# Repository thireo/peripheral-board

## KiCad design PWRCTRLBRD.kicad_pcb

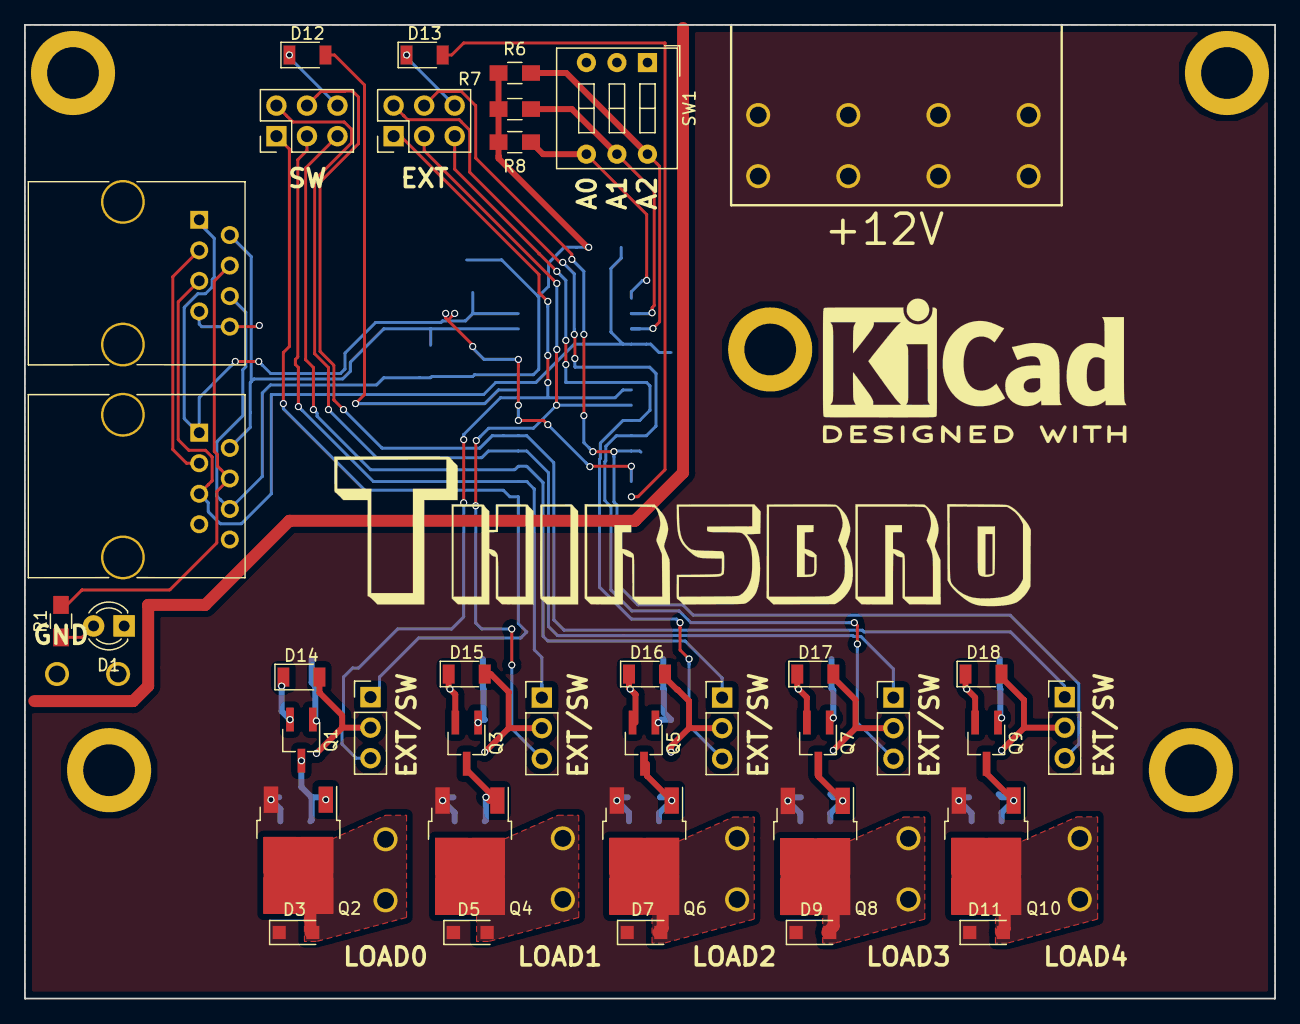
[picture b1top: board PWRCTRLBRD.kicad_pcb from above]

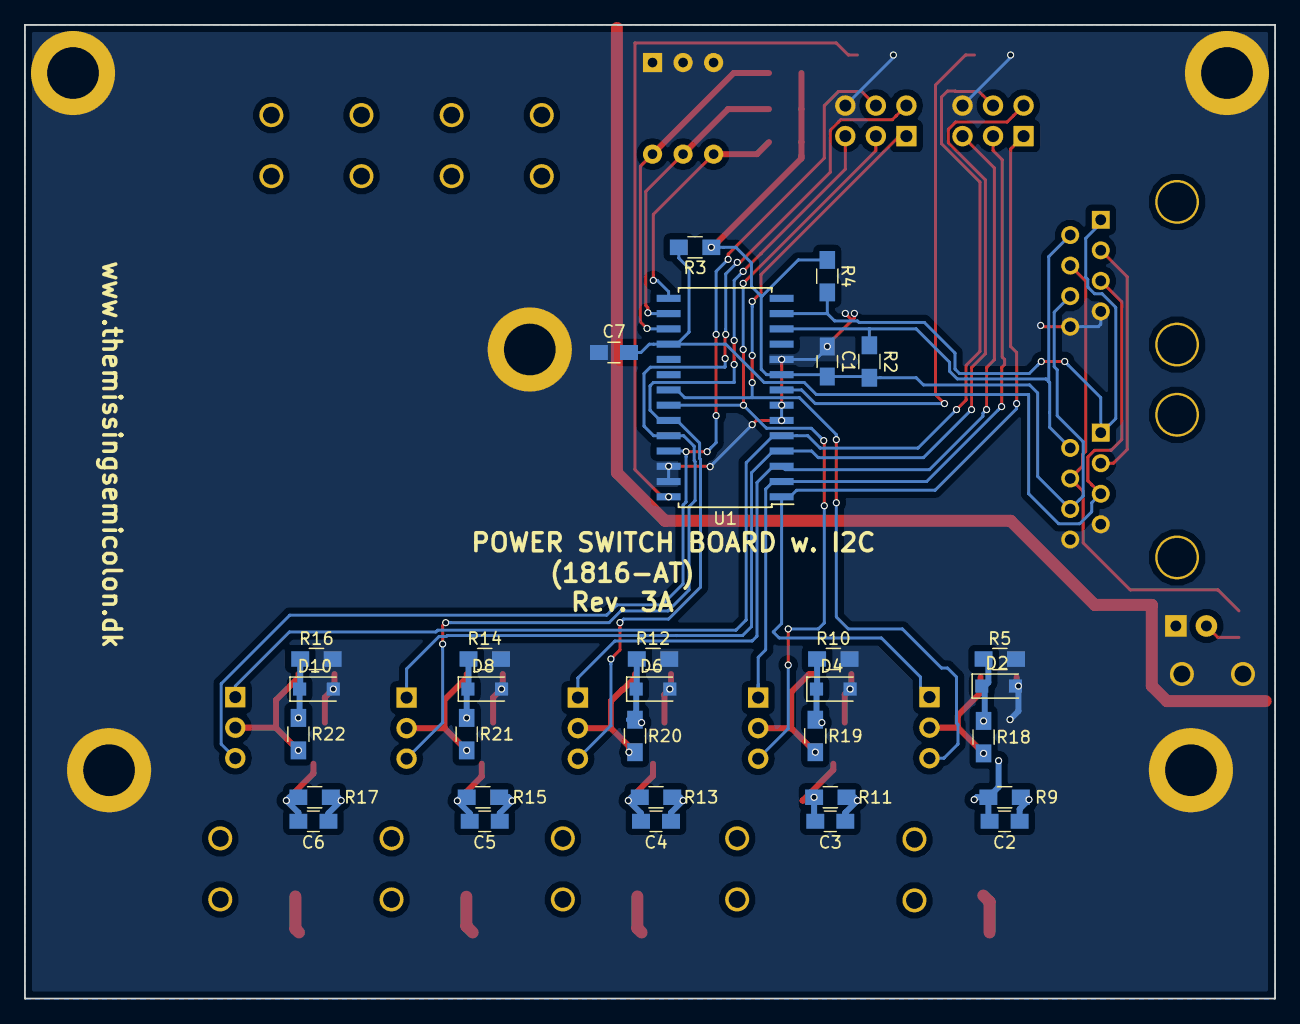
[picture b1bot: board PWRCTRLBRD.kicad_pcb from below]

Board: 2 copper layers, 104.0 x 81.0 mm, 79 parts (31 on the bottom side), 44 nets.

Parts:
C1, C2, C3, C4, C5, C6, C7: 10uF; C_0805_HandSoldering
D1: LED; LED_D3.0mm
D2, D4, D6, D8, D10: GS-TVS; D_SOD-123F
D3, D5, D7, D9, D11: DS-TVS; D_SOD-123F
D12: SW; D_1206
D13: EXT; D_1206
D14: SW0; D_1206
D15: SW1; D_1206
D16: SW2; D_1206
D17: SW3; D_1206
D18: SW4; D_1206
GND: MountingHole_4.3mm_M4_ISO14580_Pad
J1, J5, J6, J7, J8: Screw_Terminal_01x01; FASTON63951-1
J9: LOAD0; FASTON63951-1
J10: CTRL_IN1; RJ45_8
J11: CTRL0; RJ45_8
J12: LOAD1; FASTON63951-1
J13: LOAD2; FASTON63951-1
J14: LOAD3; FASTON63951-1
J15: LOAD4; FASTON63951-1
J16: EXT_IN; Pin_Header_Straight_2x03_Pitch2.54mm
J17: EXT_OUT; Pin_Header_Straight_2x03_Pitch2.54mm
JP2, JP3, JP4, JP5, JP6: EXT/SW; Pin_Header_Straight_1x03_Pitch2.54mm
Q1, Q3, Q5, Q7, Q9: NTR5103NT1G; TSOT-23_HandSoldering
Q2, Q4, Q6, Q8, Q10: TP0610T; TO-252-2
R1: R_LED; R_0805_HandSoldering
R2, R3, R4, R5, R6, R7, R8, R9, R10, R11, R12, R13, R14, R15, R16, R17: 10kohm; R_0805_HandSoldering
R18, R19, R20, R21, R22: 200ohm; R_0805_HandSoldering
SW1: SW_DIP_x03; SW_DIP_x3_W7.62mm_Slide
U1: MCP23017; SOIC-28W_7.5x17.9mm_Pitch1.27mm

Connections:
+12V: C2.1, C3.1, C4.1, C5.1, C6.1, D3.1, D5.1, D7.1, D9.1, D11.1, J5.1, J6.1, J7.1, J8.1, Q2.3, Q4.3, Q6.3, Q8.3, Q10.3, R9.1, R11.1, R13.1, R15.1, R17.1
/CS: J10.3, J11.3
/EXT0: J17.1, JP2.3, U1.21
/EXT1: J17.3, JP3.3, U1.22
/EXT2: J17.5, JP4.3, U1.23
/EXT3: J17.2, JP5.3, U1.24
/EXT4: J17.4, JP6.3, U1.25
/SCL: J10.2, J11.2, R2.2, U1.12
/SDA: J10.1, J11.1, R4.2, U1.13
/STATUS: J10.4, J11.4, R1.2
/SW0: J16.1, JP2.1, U1.1
/SW1: J16.3, JP3.1, U1.2
/SW2: J16.5, JP4.1, U1.3
/SW3: J16.2, JP5.1, U1.4
/SW4: J16.4, JP6.1, U1.5
/~RESET: C7.2, J10.5, J11.5, R3.2, U1.18
GND: C1.1, C7.1, D1.1, D2.2, D4.2, D6.2, D8.2, D10.2, D12.1, D13.1, D14.1, D15.1, D16.1, D17.1, D18.1, GND.1, J1.1, J10.7, J10.8, J11.7, J11.8, J16.6, J17.6, Q1.2, Q3.2, Q5.2, Q7.2, Q9.2, R5.2, R10.2, R12.2, R14.2, R16.2, SW1.1, SW1.2, SW1.3, U1.6, U1.7, U1.10, U1.26, U1.27
unnamed: C2.2, Q1.3, Q2.1, R9.2
unnamed: C3.2, Q3.3, Q4.1, R11.2
unnamed: C4.2, Q5.3, Q6.1, R13.2
unnamed: C5.2, Q7.3, Q8.1, R15.2
unnamed: C6.2, Q9.3, Q10.1, R17.2
unnamed: D1.2, R1.1
unnamed: D2.1, Q1.1, R5.1, R18.1
unnamed: D3.2, J9.1, Q2.2
unnamed: D4.1, Q3.1, R10.1, R19.1
unnamed: D5.2, J12.1, Q4.2
unnamed: D6.1, Q5.1, R12.1, R20.1
unnamed: D7.2, J13.1, Q6.2
unnamed: D8.1, Q7.1, R14.1, R21.1
unnamed: D9.2, J14.1, Q8.2
unnamed: D10.1, Q9.1, R16.1, R22.1
unnamed: D11.2, J15.1, Q10.2
unnamed: D12.2, U1.8
unnamed: D13.2, U1.28
unnamed: D14.2, JP2.2, R18.2
unnamed: D15.2, JP3.2, R19.2
unnamed: D16.2, JP4.2, R20.2
unnamed: D17.2, JP5.2, R21.2
unnamed: D18.2, JP6.2, R22.2
unnamed: R6.2, SW1.6, U1.17
unnamed: R7.2, SW1.5, U1.16
unnamed: R8.2, SW1.4, U1.15
VCC: C1.2, J10.6, J11.6, R2.1, R3.1, R4.1, R6.1, R7.1, R8.1, U1.9

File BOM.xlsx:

Reference | Value | Footprint | Quantity | Price (EURO) | Total (EURO) | Mouser Part No. | Datasheet
C1-C7 | 10uF | Capacitors_SMD:C_0805_HandSoldering | 7 | 0.153 | 1.071 | 581-0805YD106K
D1 | LED | LEDs:LED_D3.0mm | 1 | 7.0000000000000007E-2 | 7.0000000000000007E-2 | 696-SSL-LX3044SGC
D2+D4+D6+D8+D10 | GS-TVS | SOD-123W | 5 | 0.34899999999999998 | 1.7449999999999999 | 771-PTVS16VS1UR115 | http://www.mouser.com/ds/2/302/PTVSXS1UR_SER-104409.pdf
D3+D5+D7+D9+D11 | DS-TVS | SOD-123W | 5 | 0.34899999999999998 | 1.7449999999999999 | 771-PTVS16VS1UR115
J10 | CTRL_IN1 | Connect:RJ45_8 | 1 | 0.434 | 0.434 | 649-54601-908WPLF | http://www.mouser.com/ds/2/18/c-bmj-0051-1003727.pdf
J11 | CTRL0 | Connect:RJ45_8 | 1 | 0.434 | 0.434 | 649-54601-908WPLF
J1+J5-J9+J12-J15 | LOAD0-4+GND+4x12V | athir:FASTON63951-1 | 10 | 0.1 | 1 | 571-63951-1-CT
J16 | EXT_IN | Pin_Headers:Pin_Header_Straight_2x03_Pitch2.54mm | 1 | 0.79100000000000004 | 0.79100000000000004 | 649-87606-303LF | http://www.mouser.com/ds/2/18/bus-12-055-946221.pdf
J17 | EXT_OUT | Pin_Headers:Pin_Header_Straight_2x03_Pitch2.54mm | 1 | 0.79100000000000004 | 0.79100000000000004 | 649-87606-303LF
JP2-JP6 | EXT/SW | Pin_Headers:Pin_Header_Straight_1x03_Pitch2.54mm | 5 | 0.11899999999999999 | 0.59499999999999997 | 571-28815452 | http://www.mouser.com/ds/2/418/NG_CD_881545_K4-636856.pdf
Q1 | IRF540N | TO_SOT_Packages_SMD:SOT-23_Handsoldering | 1 | 0.111 | 0.111 | 863-NTR5103NT1G | http://www.mouser.com/ds/2/308/NTR5103N-D-600006.pdf
Q2 | TP0610T | TO_SOT_Packages_SMD:TO-252-2 | 1 | 1.28 | 1.28 | 726-IPD90P03P4L04 | http://www.mouser.com/ds/2/196/Infineon-IPD90P03P4_04-DS-v01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
Q3 | IRF540N | TO_SOT_Packages_SMD:SOT-23_Handsoldering | 1 | 0.111 | 0.111 | 863-NTR5103NT1G
Q4 | TP0610T | TO_SOT_Packages_SMD:TO-252-2 | 1 | 1.28 | 1.28 | 726-IPD90P03P4L04
Q5 | IRF540N | TO_SOT_Packages_SMD:SOT-23_Handsoldering | 1 | 0.111 | 0.111 | 863-NTR5103NT1G
Q6 | TP0610T | TO_SOT_Packages_SMD:TO-252-2 | 1 | 0.111 | 0.111 | 726-IPD90P03P4L04
Q7 | IRF540N | TO_SOT_Packages_SMD:SOT-23_Handsoldering | 1 | 0.111 | 0.111 | 863-NTR5103NT1G
Q8 | TP0610T | TO_SOT_Packages_SMD:TO-252-2 | 1 | 1.28 | 1.28 | 726-IPD90P03P4L04
Q9 | IRF540N | TO_SOT_Packages_SMD:SOT-23_Handsoldering | 1 | 0.111 | 0.111 | 863-NTR5103NT1G
Q10 | TP0610T | TO_SOT_Packages_SMD:TO-252-2 | 1 | 1.28 | 1.28 | 726-IPD90P03P4L04
R1 | R_LED | Resistors_SMD:R_0805_HandSoldering | 1 | 0.111 | 0.111
R2-R17 | 10kohm | Resistors_SMD:R_0805_HandSoldering | 16 | 8.5000000000000006E-2 | 1.36 | 603-RC0805FR-0710KL
R18-R22 | 200ohm | Resistors_SMD:R_0805_HandSoldering | 5 | 0.111 | 0.55500000000000005 | 660-RK73B2ATTD201J
SW1 | SW_DIP_x03 | Buttons_Switches_ThroughHole:SW_DIP_x3_W7.62mm_Slide | 1 | 1.28 | 1.28 | 774-206312 | http://www.mouser.com/ds/2/96/206-208-1132818.pdf
U1 | MCP23017 | Housings_SOIC:SOIC-28W_7.5x17.9mm_Pitch1.27mm | 1 | 1.07 | 1.07 | 579-MCP23017-E/SO | http://www.mouser.com/ds/2/268/20001952C-1129816.pdf
 |  |  | 71 |  | 18.838000000000005
